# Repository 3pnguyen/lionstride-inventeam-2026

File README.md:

# lionstride-inventeam-2026

## Branch for the source code of the app

 <!-- - -->  

<!-- Badeges from https://gprm.itsvg.in and https://github.com/Ileriayo/markdown-badges  -->

<div align="center">
    
</div>

## Purpose 

The app is used to remotely control the device via Bluetooth. After receiving data, it will process and store it. 

## Changelog for the code

* 4.10.26 - Initialization of the app on the repository
* 5.18.26 - Many changes to the app, including:
    * Added patient profiles
    * Added different detection methods
    * Added pressure sensing compatability
    * UI changes
    * Fixed bluetooth
    * Added functionality to send commands over bluetooth
    * Added a live monitor to watch pressure and temperature matrices actively

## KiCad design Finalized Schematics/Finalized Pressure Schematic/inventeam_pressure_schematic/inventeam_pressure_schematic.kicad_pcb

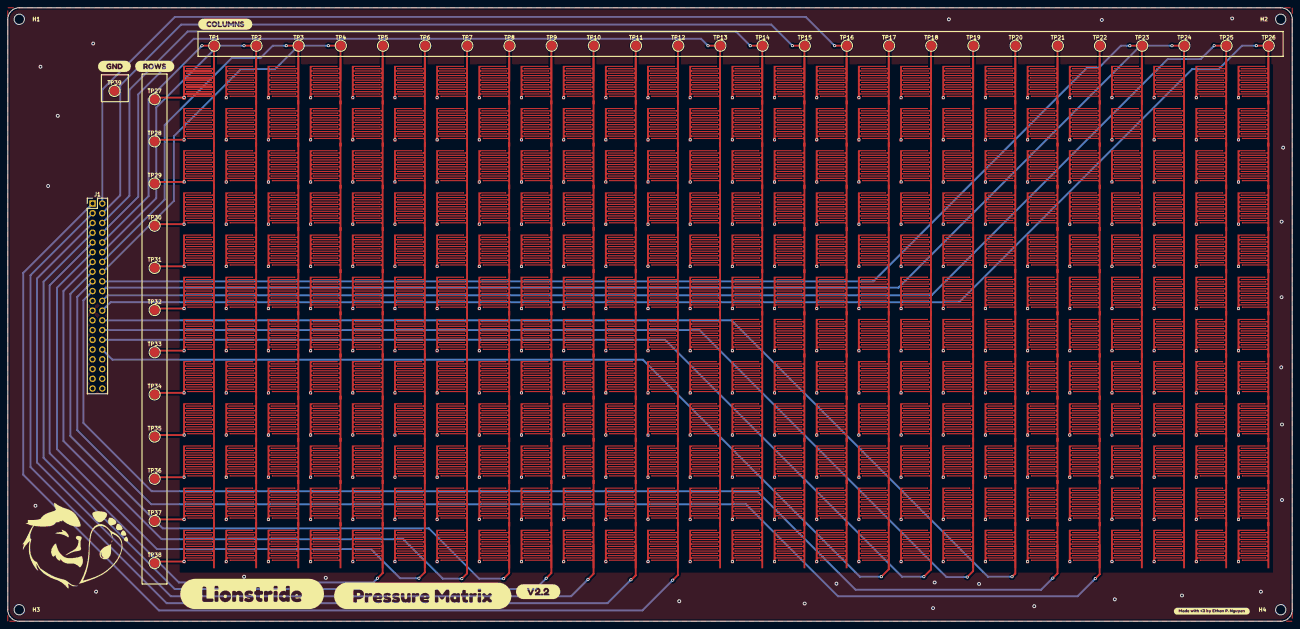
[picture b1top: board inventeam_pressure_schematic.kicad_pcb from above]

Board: 4 copper layers, 335.0 x 160.0 mm, 51 parts (0 on the bottom side), 39 nets.

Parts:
H1, H2, H3, H4: MountingHole; MountingHole_2.7mm_M2.5
J1: Conn_02x20_Odd_Even; PinHeader_2x20_P2.54mm_Vertical
TP1, TP2, TP3, TP4, TP5, TP6, TP7, TP8, TP9, TP10, TP11, TP12, TP13, TP14, TP15, TP16, TP17, TP18, TP19, TP20, TP21, TP22, TP23, TP24, TP25, TP26, TP27, TP28, TP29, TP30, TP31, TP32, TP33, TP34, TP35, TP36, TP37, TP38, TP39: TestPoint_Probe; TestPoint_Pad_D2.5mm
kibuzzard-69F7F9B9: G***; kibuzzard-69F7F9B9
kibuzzard-69F7FA32: G***; kibuzzard-69F7FA32
kibuzzard-69F7FCC3: G***; kibuzzard-69F7FCC3
kibuzzard-69F7FCD4: G***; kibuzzard-69F7FCD4
kibuzzard-69F7FD79: G***; kibuzzard-69F7FD79
kibuzzard-69F8111F: G***; kibuzzard-69F8111F
kibuzzard-69F81189: G***; kibuzzard-69F81189

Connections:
COL_1: J1.10, TP1.1
COL_2: J1.12, TP2.1
COL_3: J1.14, TP3.1
COL_4: J1.16, TP4.1
COL_5: J1.9, TP5.1
COL_6: J1.11, TP6.1
COL_7: J1.13, TP7.1
COL_8: J1.15, TP8.1
COL_9: J1.7, TP9.1
COL_10: J1.5, TP10.1
COL_11: J1.3, TP11.1
COL_12: J1.1, TP12.1
COL_13: J1.8, TP13.1
COL_14: J1.6, TP14.1
COL_15: J1.4, TP15.1
COL_16: J1.2, TP16.1
COL_17: J1.32, TP17.1
COL_18: J1.30, TP18.1
COL_19: J1.28, TP19.1
COL_20: J1.26, TP20.1
COL_21: J1.19, TP21.1
COL_22: J1.17, TP22.1
COL_23: J1.18, TP23.1
COL_24: J1.20, TP24.1
COL_25: J1.22, TP25.1
COL_26: J1.24, TP26.1
GND: J1.23, TP39.1
ROW_1: J1.34, TP27.1
ROW_2: J1.36, TP28.1
ROW_3: J1.38, TP29.1
ROW_4: J1.40, TP30.1
ROW_5: J1.39, TP31.1
ROW_6: J1.37, TP32.1
ROW_7: J1.35, TP33.1
ROW_8: J1.33, TP34.1
ROW_9: J1.31, TP35.1
ROW_10: J1.29, TP36.1
ROW_11: J1.27, TP37.1
ROW_12: J1.25, TP38.1

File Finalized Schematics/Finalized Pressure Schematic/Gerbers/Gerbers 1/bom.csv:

Designator,Footprint,Quantity,Value,LCSC Part #
J1,PinHeader_2x20_P2.54mm_Vertical,1,Conn_02x20_Odd_Even,
"TP1, TP10, TP11, TP12, TP13, TP14, TP15, TP16, TP17, TP18, TP19, TP2, TP20, TP21, TP22, TP23, TP24, TP25, TP26, TP27, TP28, TP29, TP3, TP30, TP31, TP32, TP33, TP34, TP35, TP36, TP37, TP38, TP39, TP4, TP5, TP6, TP7, TP8, TP9",TestPoint_Pad_D2.5mm,39,TestPoint_Probe,

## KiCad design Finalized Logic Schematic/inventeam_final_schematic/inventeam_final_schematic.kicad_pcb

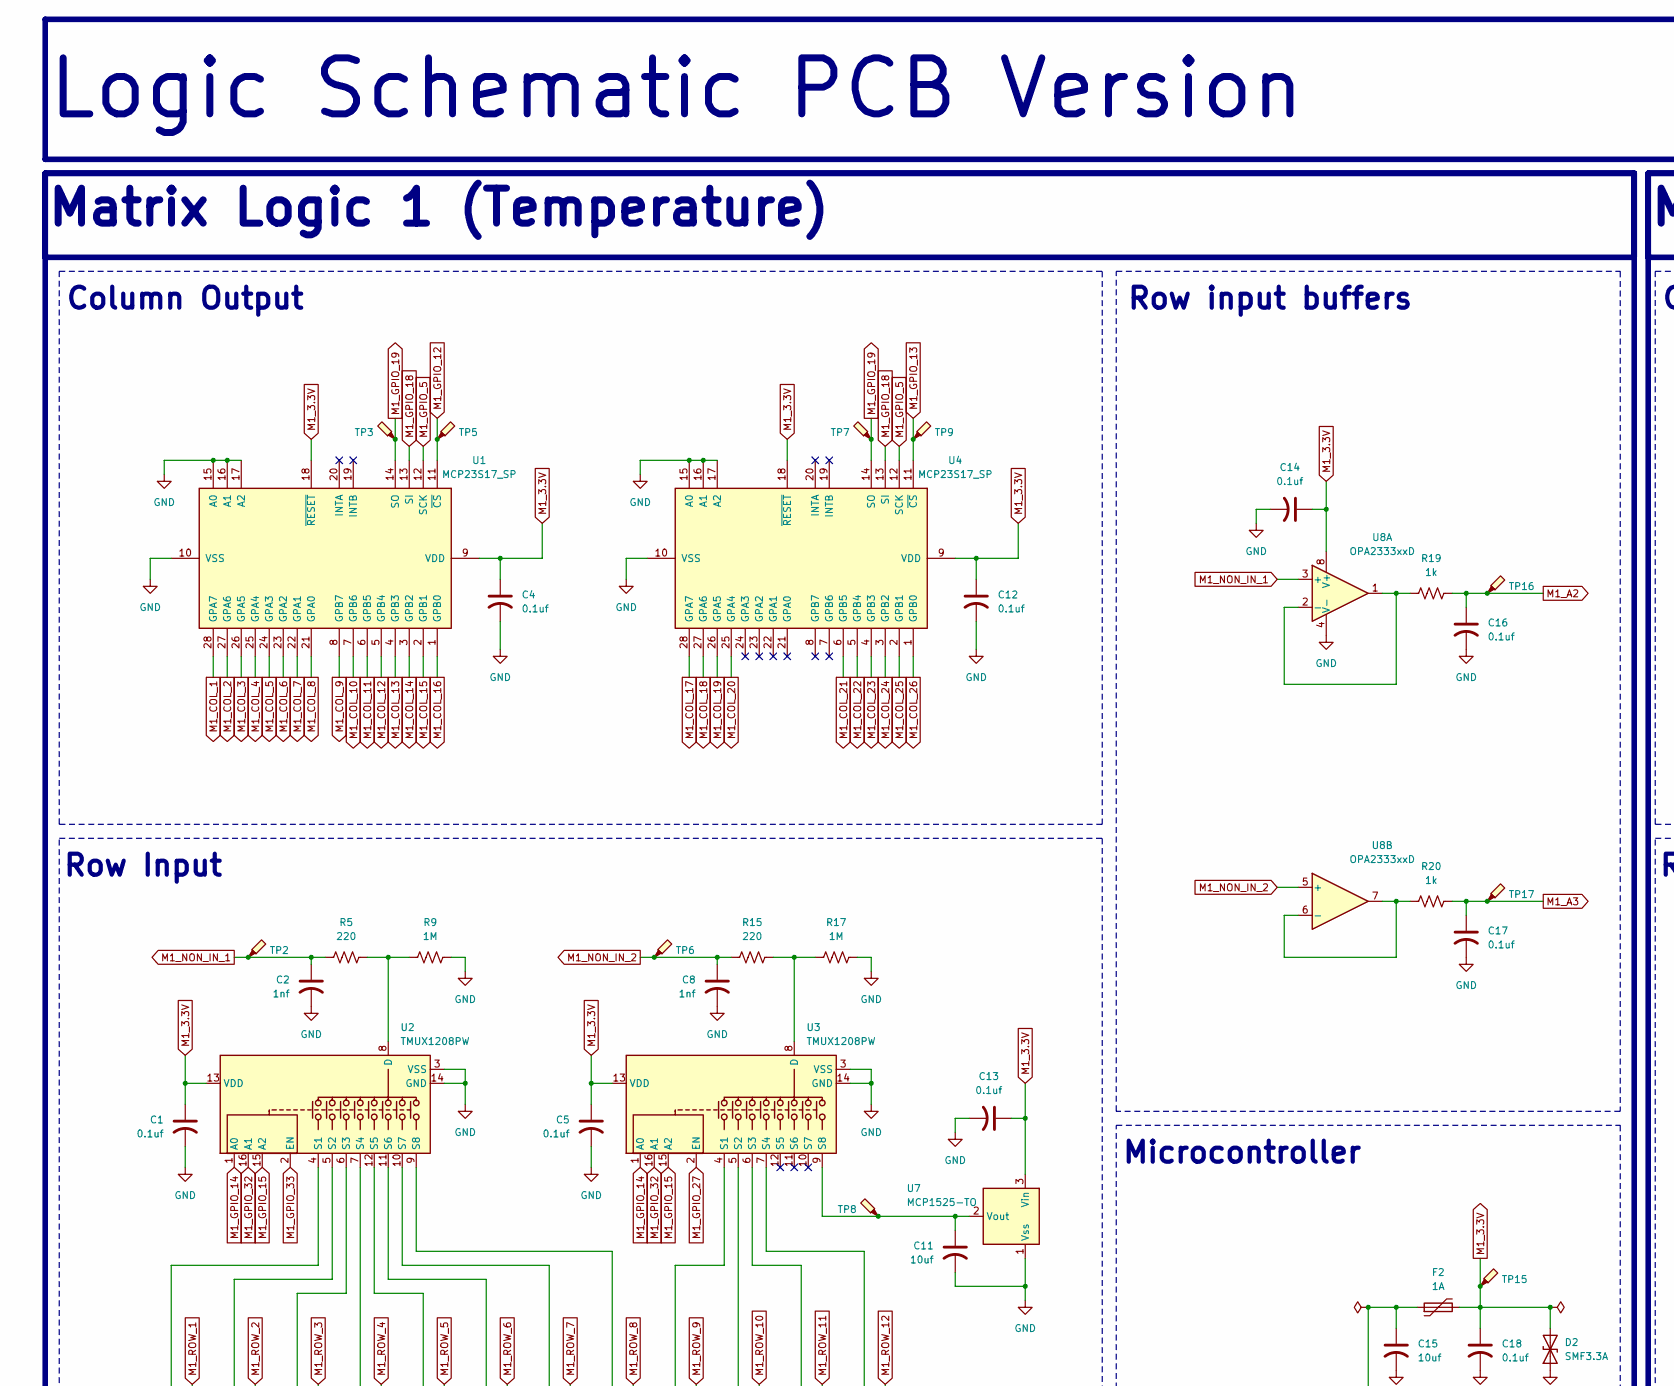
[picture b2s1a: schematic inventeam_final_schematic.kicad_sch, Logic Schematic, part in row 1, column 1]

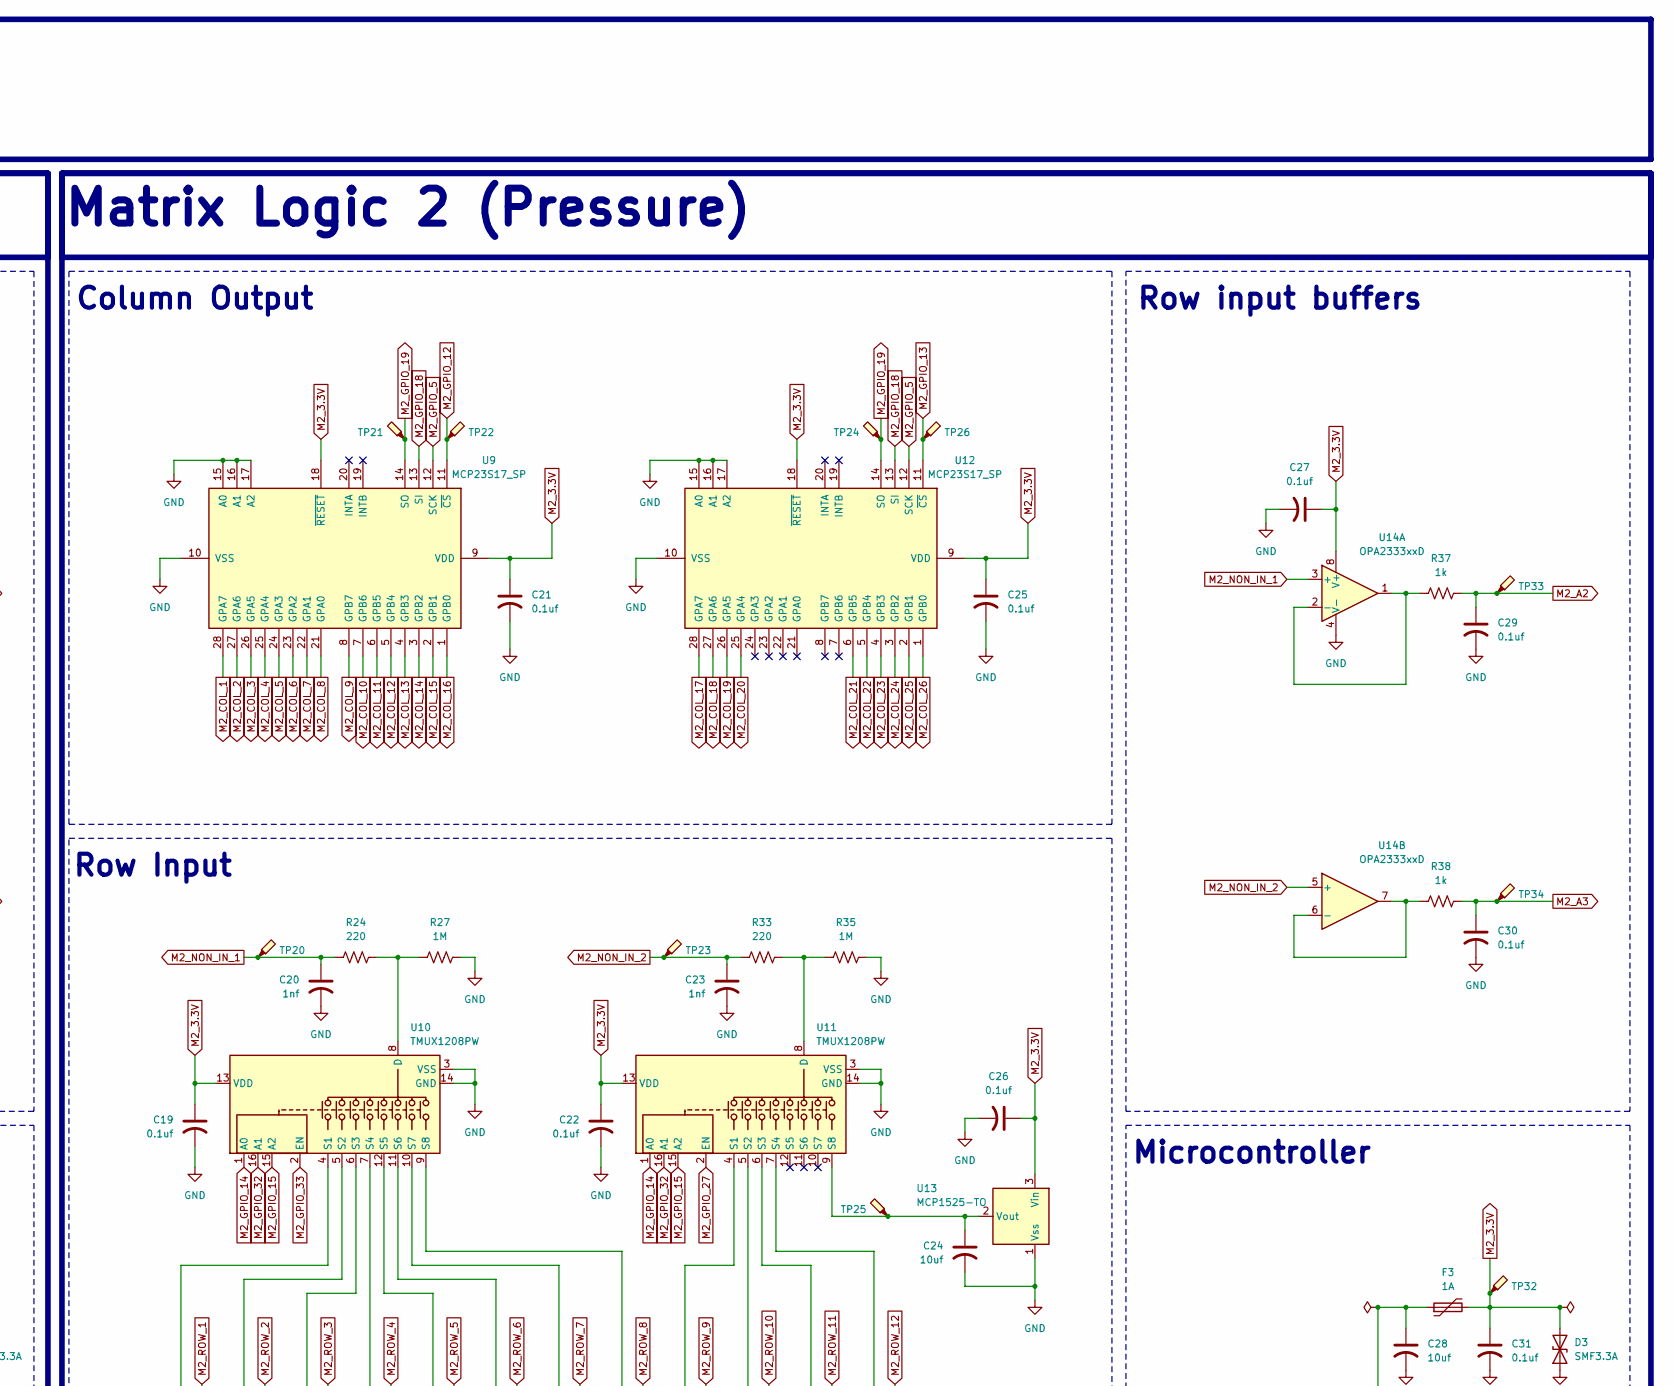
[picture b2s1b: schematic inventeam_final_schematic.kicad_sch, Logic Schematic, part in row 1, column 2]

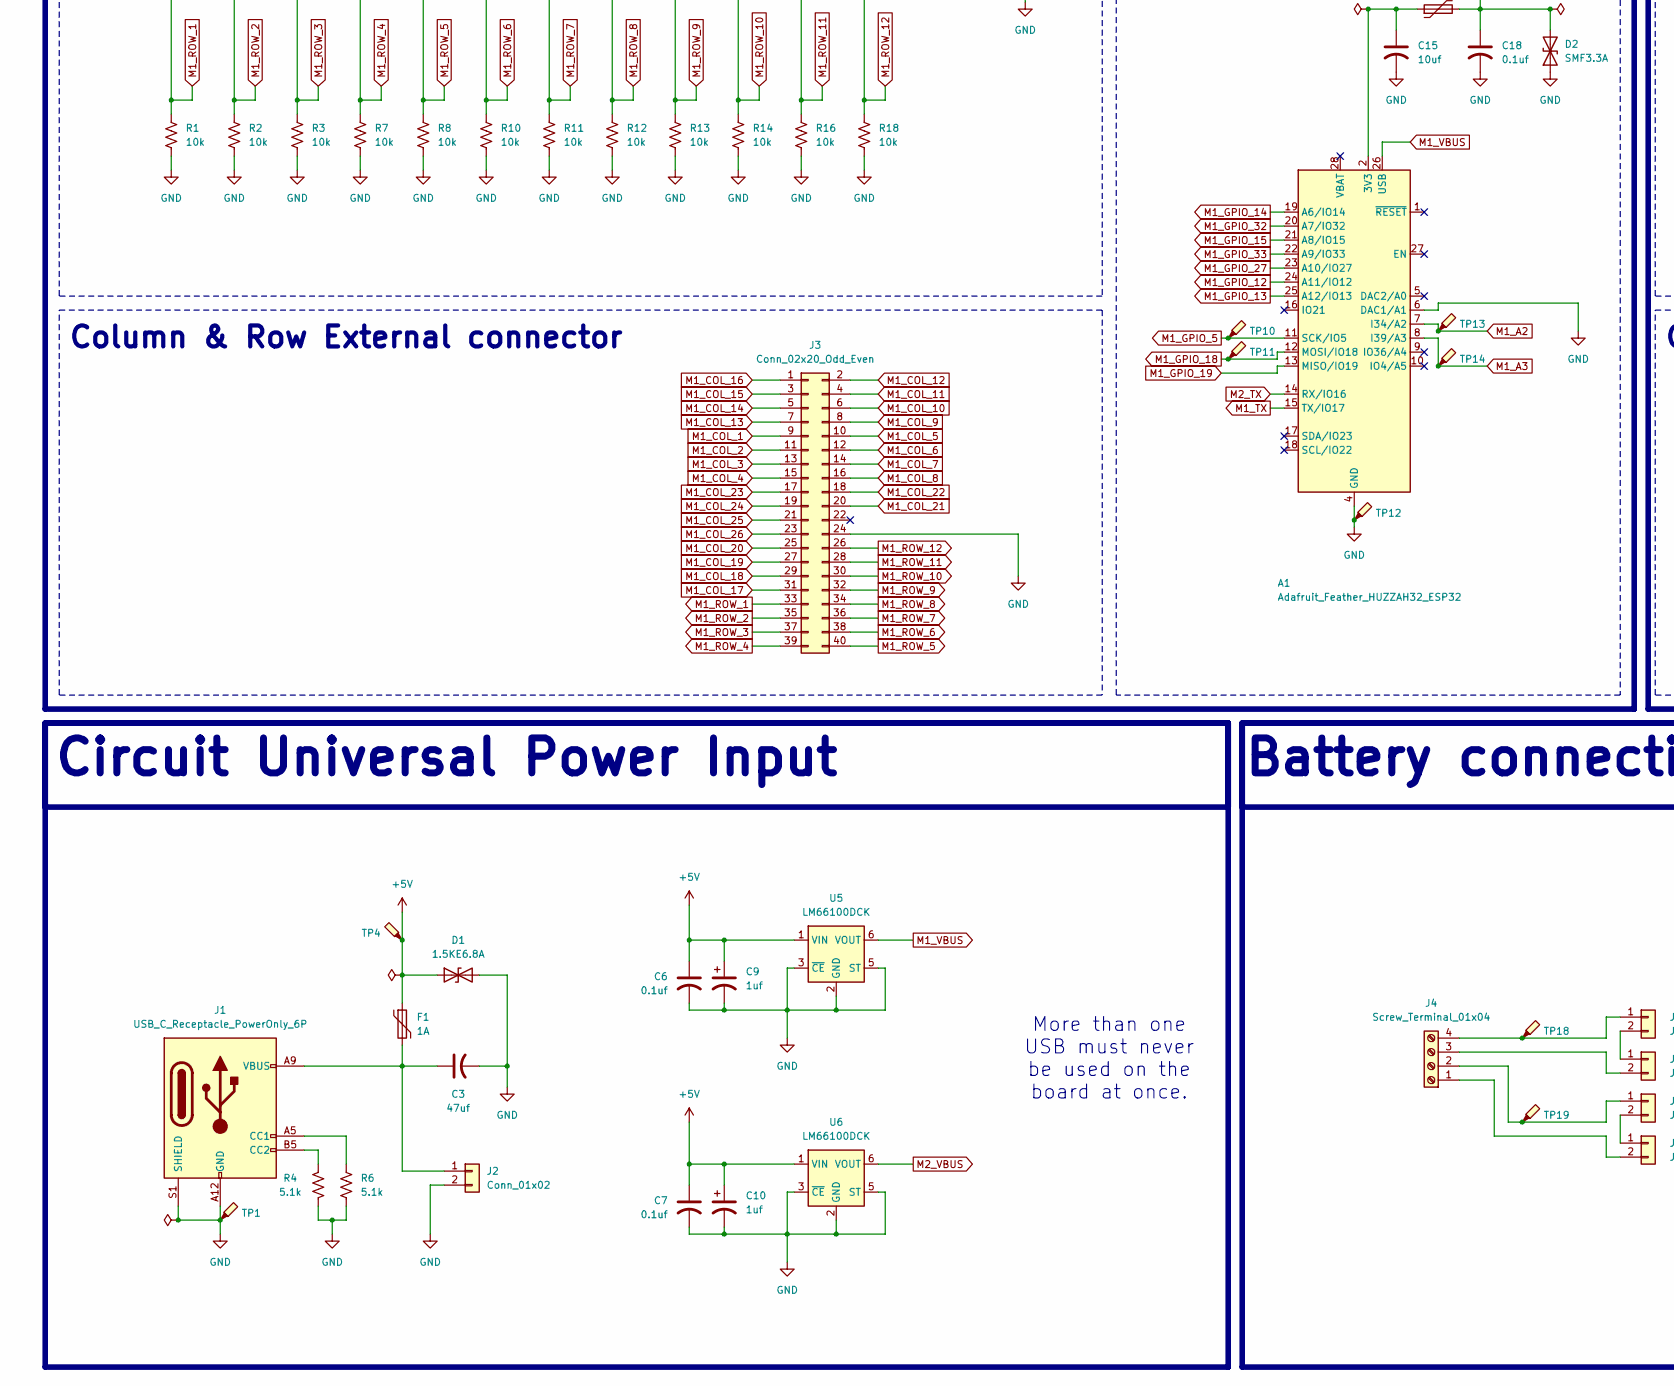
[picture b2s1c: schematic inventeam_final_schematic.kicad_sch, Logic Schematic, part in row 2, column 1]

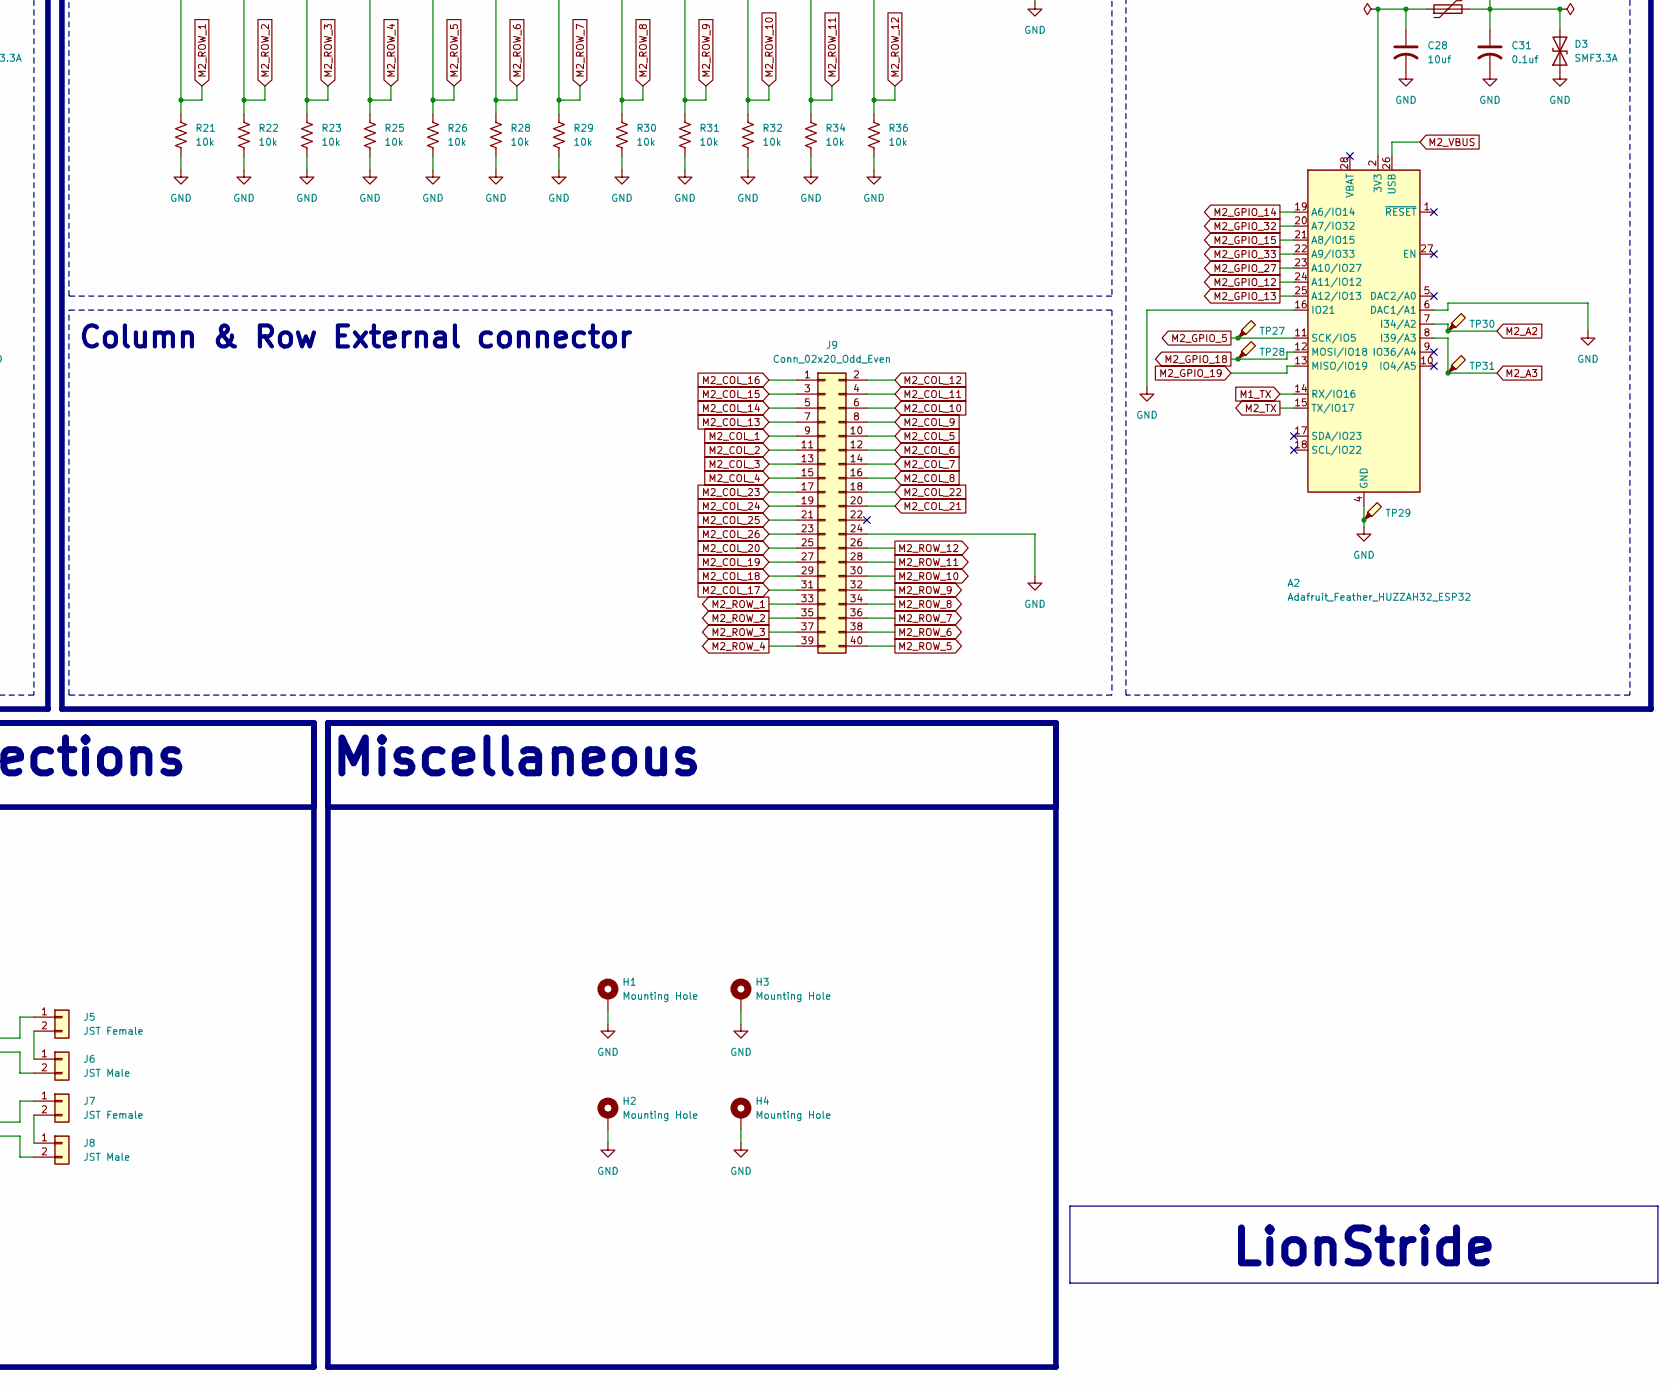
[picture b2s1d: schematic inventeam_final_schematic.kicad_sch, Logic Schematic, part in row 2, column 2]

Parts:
A1, A2: Adafruit_Feather_HUZZAH32_ESP32; Adafruit_Feather
C1, C4, C5, C6, C7, C12, C13, C14, C16, C17, C18, C19, C21, C22, C25, C26, C27, C29, C30, C31: 0.1uf; C_Disc_D5.0mm_W2.5mm_P5.00mm
C2, C8, C20, C23: 1nf; CP_Axial_L10.0mm_D4.5mm_P15.00mm_Horizontal
C3: 47uf; CP_Radial_D5.0mm_P2.50mm
C9, C10: 1uf; CP_Axial_L10.0mm_D4.5mm_P15.00mm_Horizontal
C11, C15, C24, C28: 10uf; C_Disc_D5.0mm_W2.5mm_P2.50mm
D1: 1.5KE6.8A; D_DO-201_P15.24mm_Horizontal
D2, D3: SMF3.3A; D_SOD-123F
F1, F2, F3: 1A; X16 GF100
H1, H2, H3, H4: Mounting Hole; MountingHole_2.5mm_Pad
J1: USB_C_Receptacle_PowerOnly_6P; USB_C_Receptacle_GCT_USB4125-xx-x_6P_TopMnt_Horizontal
J2: Conn_01x02; PinHeader_1x02_P2.54mm_Vertical
J3, J9: Conn_02x20_Odd_Even; PinHeader_2x20_P2.54mm_Vertical
J4: Screw_Terminal_01x04; TerminalBlock_Xinya_XY308-2.54-4P_1x04_P2.54mm_Horizontal
J5, J7: JST Female; PinHeader_1x02_P2.54mm_Vertical
J6, J8: JST Male; PinHeader_1x02_P2.54mm_Vertical
R1, R2, R3, R7, R8, R10, R11, R12, R13, R14, R16, R18, R21, R22, R23, R25, R26, R28, R29, R30, R31, R32, R34, R36: 10k; R_Axial_DIN0207_L6.3mm_D2.5mm_P7.62mm_Horizontal
R4, R6: 5.1k; R_Axial_DIN0207_L6.3mm_D2.5mm_P7.62mm_Horizontal
R5, R15, R24, R33: 220; R_Axial_DIN0207_L6.3mm_D2.5mm_P10.16mm_Horizontal
R9, R17, R27, R35: 1M; R_Axial_DIN0207_L6.3mm_D2.5mm_P7.62mm_Horizontal
R19, R20, R37, R38: 1k; R_Axial_DIN0207_L6.3mm_D2.5mm_P7.62mm_Horizontal
TP1, TP2, TP3, TP4, TP5, TP6, TP7, TP8, TP9, TP10, TP11, TP12, TP13, TP14, TP15, TP16, TP17, TP18, TP19, TP20, TP21, TP22, TP23, TP24, TP25, TP26, TP27, TP28, TP29, TP30, TP31, TP32, TP33, TP34: TestPoint_Probe; TestPoint_Pad_D1.0mm
U1, U4, U9, U12: MCP23S17_SP; DIP-28_W7.62mm
U2, U3, U10, U11: TMUX1208PW; TSSOP-16_4.4x5mm_P0.65mm
U5, U6: LM66100DCK; SOT-363_SC-70-6
U7, U13: MCP1525-TO; TO-92_Inline
U8, U14: OPA2333xxD; SOIC-8_3.9x4.9mm_P1.27mm

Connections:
+5V: C6.1, C7.1, C9.1, C10.1, D1.1 (A1), F1.1, TP4.1, U5.1 (VIN), U6.1 (VIN)
GND: A1.4 (GND), A1.6 (DAC1/A1), A2.4 (GND), A2.6 (DAC1/A1), A2.16 (IO21), C1.2, C2.2, C3.2, C4.2, C5.2, C6.2, C7.2, C8.2, C9.2, C10.2, C11.2, C12.2, C13.2, C14.2, C15.2, C16.2, C17.2, C18.2, C19.2, C20.2, C21.2, C22.2, C23.2, C24.2, C25.2, C26.2, C27.2, C28.2, C29.2, C30.2, C31.2, D1.2 (A2), D2.1 (A1), D3.1 (A1), H1.1, H2.1, H3.1, H4.1, J1.A12 (GND), J1.B12 (GND), J1.S1 (SHIELD), J2.2, J3.24, J9.24, R1.2, R2.2, R3.2, R4.2, R6.2, R7.2, R8.2, R9.2, R10.2, R11.2, R12.2, R13.2, R14.2, R16.2, R17.2, R18.2, R21.2, R22.2, R23.2, R25.2, R26.2, R27.2, R28.2, R29.2, R30.2, R31.2, R32.2, R34.2, R35.2, R36.2, TP1.1, TP12.1, TP29.1, U1.10 (VSS), U1.15 (A0), U1.16 (A1), U1.17 (A2), U2.3 (VSS), U2.14 (GND), U3.3 (VSS), U3.14 (GND), U4.10 (VSS), U4.15 (A0), U4.16 (A1), U4.17 (A2), U5.2 (GND), U5.3 (~CE), U5.5 (ST), U6.2 (GND), U6.3 (~CE), U6.5 (ST), U7.1 (Vss), U8.4 (V-), U9.10 (VSS), U9.15 (A0), U9.16 (A1), U9.17 (A2), U10.3 (VSS), U10.14 (GND), U11.3 (VSS), U11.14 (GND), U12.10 (VSS), U12.15 (A0), U12.16 (A1), U12.17 (A2), U13.1 (Vss), U14.4 (V-)
M1_3.3V: C1.1, C4.1, C5.1, C12.1, C13.1, C14.1, C18.1, D2.2 (A2), F2.2, TP15.1, U1.9 (VDD), U1.18 (~RESET), U2.13 (VDD), U3.13 (VDD), U4.9 (VDD), U4.18 (~RESET), U7.3 (Vin), U8.8 (V+)
M1_A2: A1.7 (I34/A2), C16.1, R19.2, TP13.1, TP16.1
M1_A3: A1.8 (I39/A3), C17.1, R20.2, TP14.1, TP17.1
M1_COL_1: J3.9, U1.28 (GPA7)
M1_COL_2: J3.11, U1.27 (GPA6)
M1_COL_3: J3.13, U1.26 (GPA5)
M1_COL_4: J3.15, U1.25 (GPA4)
M1_COL_5: J3.10, U1.24 (GPA3)
M1_COL_6: J3.12, U1.23 (GPA2)
M1_COL_7: J3.14, U1.22 (GPA1)
M1_COL_8: J3.16, U1.21 (GPA0)
M1_COL_9: J3.8, U1.8 (GPB7)
M1_COL_10: J3.6, U1.7 (GPB6)
M1_COL_11: J3.4, U1.6 (GPB5)
M1_COL_12: J3.2, U1.5 (GPB4)
M1_COL_13: J3.7, U1.4 (GPB3)
M1_COL_14: J3.5, U1.3 (GPB2)
M1_COL_15: J3.3, U1.2 (GPB1)
M1_COL_16: J3.1, U1.1 (GPB0)
M1_COL_17: J3.31, U4.28 (GPA7)
M1_COL_18: J3.29, U4.27 (GPA6)
M1_COL_19: J3.27, U4.26 (GPA5)
M1_COL_20: J3.25, U4.25 (GPA4)
M1_COL_21: J3.20, U4.6 (GPB5)
M1_COL_22: J3.18, U4.5 (GPB4)
M1_COL_23: J3.17, U4.4 (GPB3)
M1_COL_24: J3.19, U4.3 (GPB2)
M1_COL_25: J3.21, U4.2 (GPB1)
M1_COL_26: J3.23, U4.1 (GPB0)
M1_GPIO_5: A1.11 (SCK/IO5), TP10.1, U1.12 (SCK), U4.12 (SCK)
M1_GPIO_12: A1.24 (A11/IO12), TP5.1, U1.11 (~CS)
M1_GPIO_13: A1.25 (A12/IO13), TP9.1, U4.11 (~CS)
M1_GPIO_14: A1.19 (A6/IO14), U2.1 (A0), U3.1 (A0)
M1_GPIO_15: A1.21 (A8/IO15), U2.15 (A2), U3.15 (A2)
M1_GPIO_18: A1.12 (MOSI/IO18), TP11.1, U1.13 (SI), U4.13 (SI)
M1_GPIO_19: A1.13 (MISO/IO19), TP3.1, TP7.1, U1.14 (SO), U4.14 (SO)
M1_GPIO_27: A1.23 (A10/IO27), U3.2 (EN)
M1_GPIO_32: A1.20 (A7/IO32), U2.16 (A1), U3.16 (A1)
M1_GPIO_33: A1.22 (A9/IO33), U2.2 (EN)
M1_NON_IN_1: C2.1, R5.1, TP2.1, U8.3 (+)
M1_NON_IN_2: C8.1, R15.1, TP6.1, U8.5 (+)
M1_ROW_1: J3.33, R1.1, U2.4 (S1)
M1_ROW_2: J3.35, R2.1, U2.5 (S2)
M1_ROW_3: J3.37, R3.1, U2.6 (S3)
M1_ROW_4: J3.39, R7.1, U2.7 (S4)
M1_ROW_5: J3.40, R8.1, U2.12 (S5)
M1_ROW_6: J3.38, R10.1, U2.11 (S6)
M1_ROW_7: J3.36, R11.1, U2.10 (S7)
M1_ROW_8: J3.34, R12.1, U2.9 (S8)
M1_ROW_9: J3.32, R13.1, U3.4 (S1)
M1_ROW_10: J3.30, R14.1, U3.5 (S2)
M1_ROW_11: J3.28, R16.1, U3.6 (S3)
M1_ROW_12: J3.26, R18.1, U3.7 (S4)
M1_TX: A1.15 (TX/IO17), A2.14 (RX/IO16)
M1_VBUS: A1.26 (USB), U5.6 (VOUT)
M2_3.3V: C19.1, C21.1, C22.1, C25.1, C26.1, C27.1, C31.1, D3.2 (A2), F3.2, TP32.1, U9.9 (VDD), U9.18 (~RESET), U10.13 (VDD), U11.13 (VDD), U12.9 (VDD), U12.18 (~RESET), U13.3 (Vin), U14.8 (V+)
M2_A2: A2.7 (I34/A2), C29.1, R37.2, TP30.1, TP33.1
M2_A3: A2.8 (I39/A3), C30.1, R38.2, TP31.1, TP34.1
M2_COL_1: J9.9, U9.28 (GPA7)
M2_COL_2: J9.11, U9.27 (GPA6)
M2_COL_3: J9.13, U9.26 (GPA5)
M2_COL_4: J9.15, U9.25 (GPA4)
M2_COL_5: J9.10, U9.24 (GPA3)
M2_COL_6: J9.12, U9.23 (GPA2)
M2_COL_7: J9.14, U9.22 (GPA1)
M2_COL_8: J9.16, U9.21 (GPA0)
M2_COL_9: J9.8, U9.8 (GPB7)
M2_COL_10: J9.6, U9.7 (GPB6)
M2_COL_11: J9.4, U9.6 (GPB5)
M2_COL_12: J9.2, U9.5 (GPB4)
M2_COL_13: J9.7, U9.4 (GPB3)
M2_COL_14: J9.5, U9.3 (GPB2)
M2_COL_15: J9.3, U9.2 (GPB1)
M2_COL_16: J9.1, U9.1 (GPB0)
M2_COL_17: J9.31, U12.28 (GPA7)
M2_COL_18: J9.29, U12.27 (GPA6)
M2_COL_19: J9.27, U12.26 (GPA5)
M2_COL_20: J9.25, U12.25 (GPA4)
M2_COL_21: J9.20, U12.6 (GPB5)
M2_COL_22: J9.18, U12.5 (GPB4)
M2_COL_23: J9.17, U12.4 (GPB3)
M2_COL_24: J9.19, U12.3 (GPB2)
M2_COL_25: J9.21, U12.2 (GPB1)
M2_COL_26: J9.23, U12.1 (GPB0)
M2_GPIO_5: A2.11 (SCK/IO5), TP27.1, U9.12 (SCK), U12.12 (SCK)
M2_GPIO_12: A2.24 (A11/IO12), TP22.1, U9.11 (~CS)
M2_GPIO_13: A2.25 (A12/IO13), TP26.1, U12.11 (~CS)
M2_GPIO_14: A2.19 (A6/IO14), U10.1 (A0), U11.1 (A0)
M2_GPIO_15: A2.21 (A8/IO15), U10.15 (A2), U11.15 (A2)
M2_GPIO_18: A2.12 (MOSI/IO18), TP28.1, U9.13 (SI), U12.13 (SI)
M2_GPIO_19: A2.13 (MISO/IO19), TP21.1, TP24.1, U9.14 (SO), U12.14 (SO)
M2_GPIO_27: A2.23 (A10/IO27), U11.2 (EN)
M2_GPIO_32: A2.20 (A7/IO32), U10.16 (A1), U11.16 (A1)
M2_GPIO_33: A2.22 (A9/IO33), U10.2 (EN)
M2_NON_IN_1: C20.1, R24.1, TP20.1, U14.3 (+)
M2_NON_IN_2: C23.1, R33.1, TP23.1, U14.5 (+)
M2_ROW_1: J9.33, R21.1, U10.4 (S1)
M2_ROW_2: J9.35, R22.1, U10.5 (S2)
M2_ROW_3: J9.37, R23.1, U10.6 (S3)
M2_ROW_4: J9.39, R25.1, U10.7 (S4)
M2_ROW_5: J9.40, R26.1, U10.12 (S5)
M2_ROW_6: J9.38, R28.1, U10.11 (S6)
M2_ROW_7: J9.36, R29.1, U10.10 (S7)
M2_ROW_8: J9.34, R30.1, U10.9 (S8)
M2_ROW_9: J9.32, R31.1, U11.4 (S1)
M2_ROW_10: J9.30, R32.1, U11.5 (S2)
M2_ROW_11: J9.28, R34.1, U11.6 (S3)
M2_ROW_12: J9.26, R36.1, U11.7 (S4)
M2_TX: A1.14 (RX/IO16), A2.15 (TX/IO17)
M2_VBUS: A2.26 (USB), U6.6 (VOUT)
unnamed: A1.2 (3V3), C15.1, F2.1
unnamed: A2.2 (3V3), C28.1, F3.1
unnamed: J1.A5 (CC1), R6.1
unnamed: J1.B5 (CC2), R4.1
unnamed: C3.1, F1.2, J1.A9 (VBUS), J1.B9 (VBUS), J2.1
unnamed: J4.1, J8.2
unnamed: J4.2, J7.1, TP19.1
unnamed: J4.3, J6.2
unnamed: J4.4, J5.1, TP18.1
unnamed: J5.2, J6.1
unnamed: J7.2, J8.1
unnamed: R5.2, R9.1, U2.8 (D)
unnamed: R15.2, R17.1, U3.8 (D)
unnamed: C11.1, TP8.1, U3.9 (S8), U7.2 (Vout)
unnamed: R19.1, U8.1, U8.2 (-)
unnamed: R20.1, U8.6 (-), U8.7
unnamed: R24.2, R27.1, U10.8 (D)
unnamed: R33.2, R35.1, U11.8 (D)
unnamed: C24.1, TP25.1, U11.9 (S8), U13.2 (Vout)
unnamed: R37.1, U14.1, U14.2 (-)
unnamed: R38.1, U14.6 (-), U14.7

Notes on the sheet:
Column Output
Circuit Universal Power Input
Column & Row External connector
Matrix Logic 2 (Pressure)
Row input buffers
Microcontroller
Logic Schematic PCB Version
Miscellaneous
Matrix Logic 1 (Temperature)
LionStride
Battery connections
More than one USB must never be used on the board at once.
Row Input

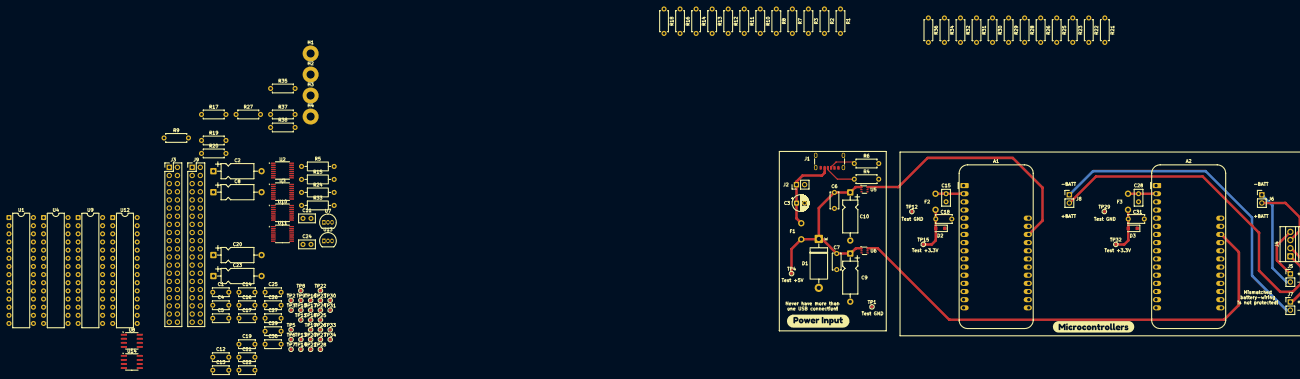
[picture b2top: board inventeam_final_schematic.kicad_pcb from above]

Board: 4 copper layers, 140 parts (0 on the bottom side), 133 nets.

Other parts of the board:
kibuzzard-69C8AE86: G***; kibuzzard-69C8AE86
kibuzzard-69C8846F: G***; kibuzzard-69C8846F
